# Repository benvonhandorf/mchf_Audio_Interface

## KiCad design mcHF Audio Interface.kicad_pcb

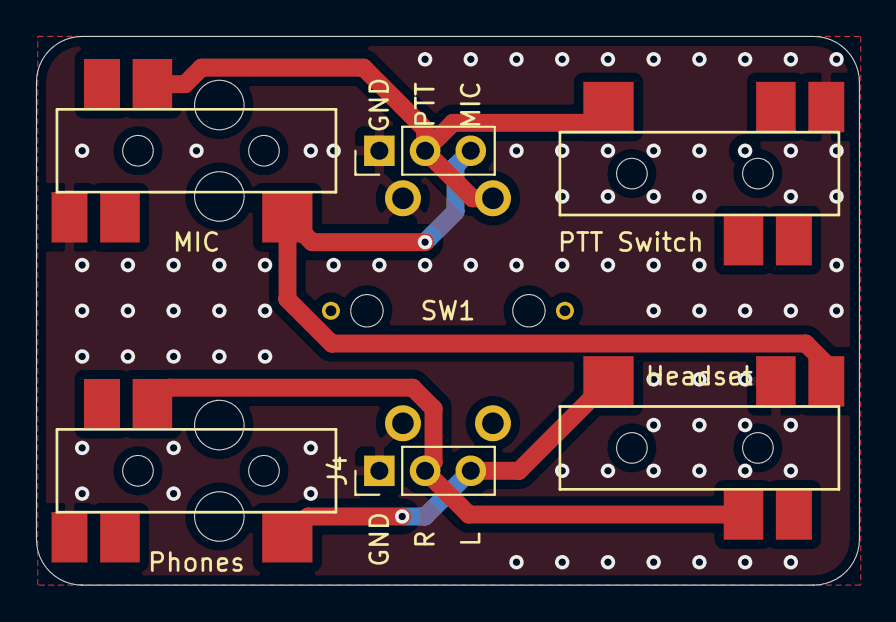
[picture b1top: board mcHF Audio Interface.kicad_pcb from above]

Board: 2 copper layers, 45.7 x 30.5 mm, 7 parts (0 on the bottom side), 5 nets.

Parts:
Headset: Headset; SJ-43515RS-SMT-TR
J3: MIC_CONN; PinHeader_1x03_P2.54mm_Vertical
J4: PHONE_CONN; PinHeader_1x03_P2.54mm_Vertical
MIC: MIC; SJ-43515RS-SMT-TR
PTT Switch: PTT; SJ-43515RS-SMT-TR
Phones: PHONE; SJ-43515RS-SMT-TR
SW1: PTT; TacButton_12mm_12mm_LED-optional

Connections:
Audio_L: Headset.2, J4.3, Phones.2
Audio_R: Headset.3, J4.2, Phones.3
GND: Headset.4, J3.1, J4.1, MIC.1, PTT Switch.1, Phones.1, SW1.2
MIC: Headset.1, J3.3, MIC.2
PTT: J3.2, MIC.3, PTT Switch.2, SW1.1
